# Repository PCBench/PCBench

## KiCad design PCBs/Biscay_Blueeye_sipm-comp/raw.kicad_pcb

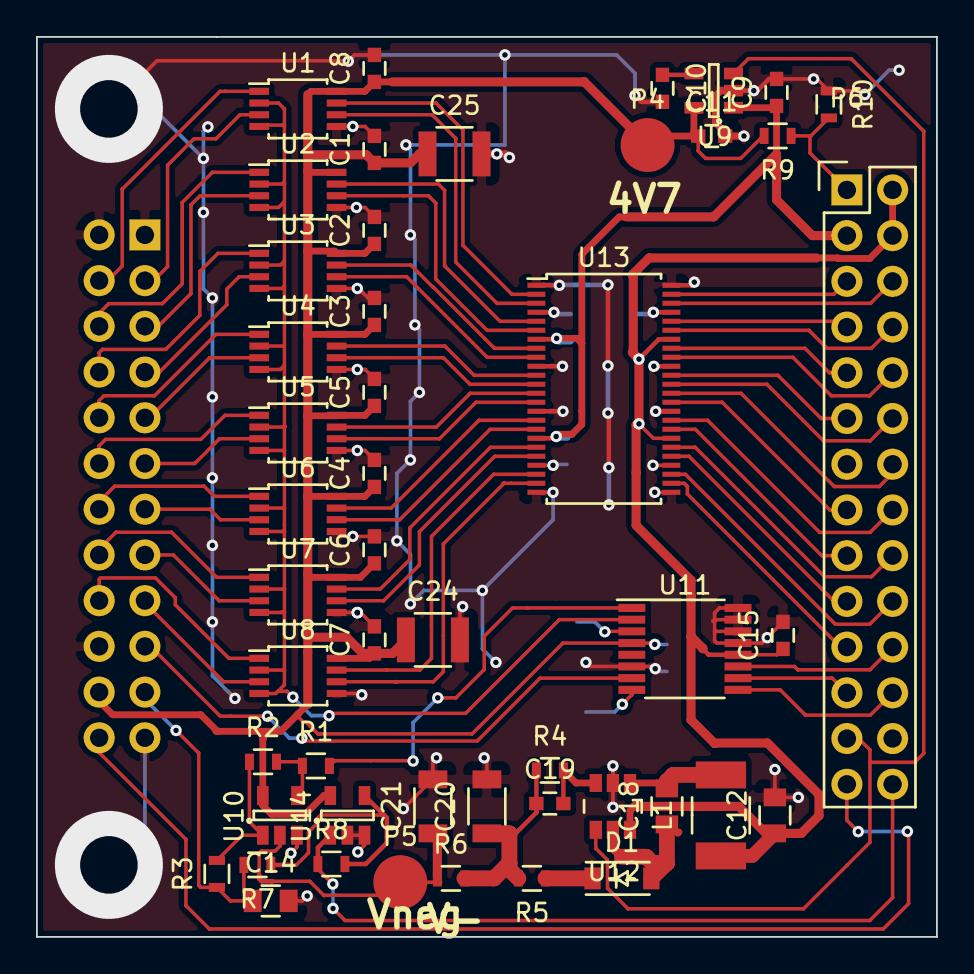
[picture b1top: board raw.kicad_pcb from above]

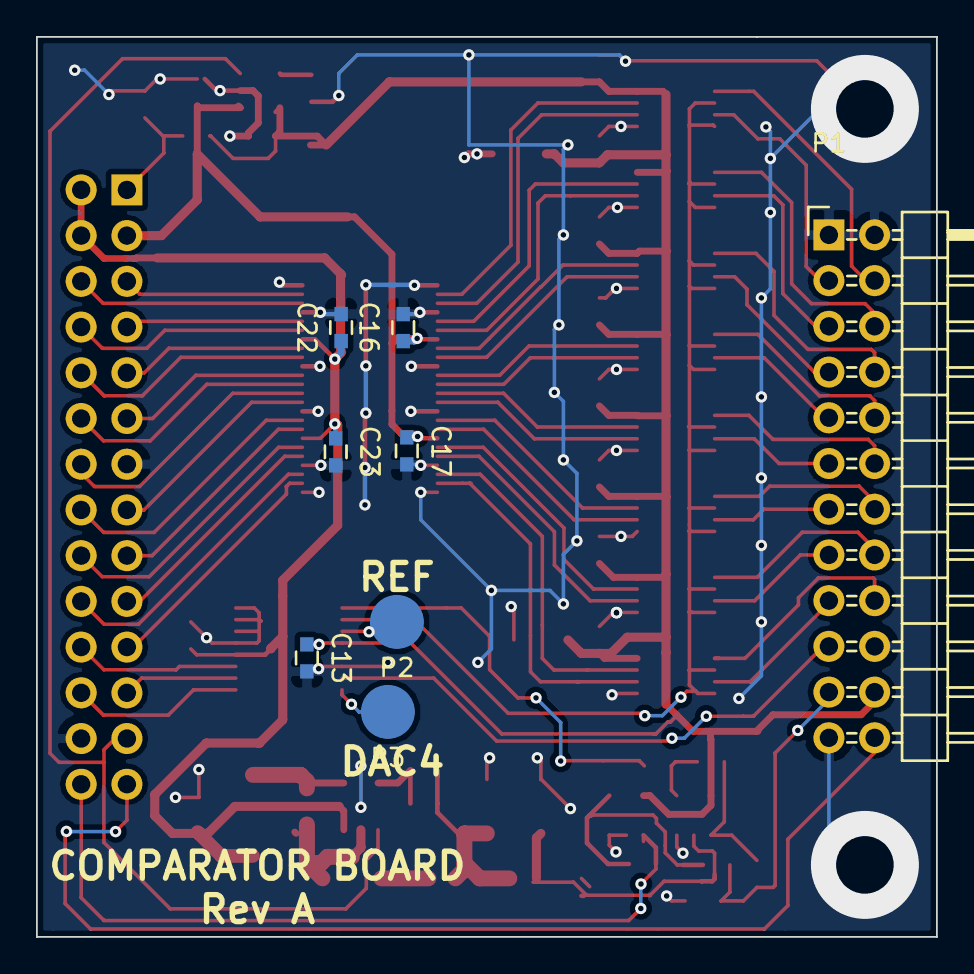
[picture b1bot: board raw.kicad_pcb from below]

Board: 2 copper layers, 50.0 x 50.0 mm, 57 parts (8 on the bottom side), 75 nets.

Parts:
C1, C2, C3, C4, C5, C6, C7, C8, C9, C11, C13, C15, C16, C17, C22, C23: 1u; C_0603
C10: 10n; C_0603
C12: 4.7u; C_0805
C14, C18: 0.1u; C_0805
C19: 5p; C_0603
C20, C21: 1u; C_1206
C24, C25: 22u; C_1210
D1: MBR0540; SOD-123
L1: 10u; Neosid_Inductor_SM-NE45_SMD1812
P1: CONN_02X12; Pin_Header_Angled_2x12
P2: REFO; Measurement_Point_Round-SMD-Pad_Big
P3: AUXDAC; Measurement_Point_Round-SMD-Pad_Big
P4: 5VA; Measurement_Point_Round-SMD-Pad_Big
P5: Vneg; Measurement_Point_Round-SMD-Pad_Big
P6: CONN_01X28; Pin_Header_Straight_2x14
R1, R3: 1k; R_0603
R2, R8: 15k; R_0603
R4: 3.4M; R_0603
R5: 39; R_0603
R6: 100; R_0603
R7: 100k; R_0603
R9, R10: 10k; R_0603
U1, U2, U3, U4, U5, U6, U7, U8: MAX9012; TSSOP-8_3x3mm_Pitch0.65mm
U9: LD3985M47R; SOT-23-5
U10: LT6015; SOT-23-5
U11: DAC7564; TSSOP-16_4.4x5mm_Pitch0.65mm
U12: LT3483; TSOT-6-MK06A
U13: SN74LVCH16T245; TSSOP-48_6.1x12.5mm_Pitch0.5mm
U14: LT6003; SOT-23-5

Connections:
+3V3: C12.1, C15.1, C22.1, C23.1, L1.1, P6.2, P6.4, U11.12, U12.6, U13.31, U13.42
+5V: C9.1, C16.1, C17.1, P6.3, U9.1, U13.7, U13.18
+5VA: C1.1, C2.1, C3.1, C4.1, C5.1, C6.1, C7.1, C8.1, C11.1, C13.1, C24.1, C25.1, P1.22, P4.1, R9.2, U1.8, U2.8, U3.8, U4.8, U5.8, U6.8, U7.8, U8.8, U9.5, U10.5, U11.4, U14.5
/AMP_1: P1.11, U5.3
/AMP_2: P1.15, U7.3
/AMP_3: P1.8, U3.1
/AMP_4: P1.9, U4.3
/AMP_5: P1.13, U6.3
/AMP_6: P1.16, U7.1
/AMP_7: P1.7, U3.3
/AMP_8: P1.10, U4.1
/AMP_9: P1.18, U8.1
/AMP_10: P1.17, U8.3
/AMP_11: P1.5, U2.3
/AMP_12: P1.6, U2.1
/AMP_13: P1.14, U6.1
/AMP_14: P1.12, U5.1
/AMP_15: P1.3, U1.3
/AMP_16: P1.4, U1.1
/COMP_1: U5.6, U13.14
/COMP_2: U7.6, U13.20
/COMP_3: U3.7, U13.8
/COMP_4: U4.6, U13.12
/COMP_5: U6.6, U13.17
/COMP_6: U7.7, U13.19
/COMP_7: U3.6, U13.9
/COMP_8: U4.7, U13.11
/COMP_9: U8.7, U13.22
/COMP_10: U8.6, U13.23
/COMP_11: U2.6, U13.6
/COMP_12: U2.7, U13.5
/COMP_13: U6.7, U13.16
/COMP_14: U5.7, U13.13
/COMP_15: U1.6, U13.3
/COMP_16: U1.7, U13.2
/DAC_Din: P6.22, U11.11
/DAC_SCLK: P6.23, U11.10
/DAC_~SYNC: P6.24, U11.9
/MON_5VA: P6.1, R9.1, R10.2
/OUT_1: P6.15, U13.35
/OUT_2: P6.19, U13.29
/OUT_3: P6.9, U13.41
/OUT_4: P6.12, U13.37
/OUT_5: P6.17, U13.32
/OUT_6: P6.18, U13.30
/OUT_7: P6.10, U13.40
/OUT_8: P6.11, U13.38
/OUT_9: P6.20, U13.27
/OUT_10: P6.21, U13.26
/OUT_11: P6.8, U13.43
/OUT_12: P6.7, U13.44
/OUT_13: P6.16, U13.33
/OUT_14: P6.14, U13.36
/OUT_15: P6.6, U13.46
/OUT_16: P6.5, U13.47
/TEMPS: P1.24, P6.27
/Vb_MON: P6.28, R8.1, U14.1
GND: C1.2, C2.2, C3.2, C4.2, C5.2, C6.2, C7.2, C8.2, C9.2, C10.2, C11.2, C12.2, C13.2, C14.2, C15.2, C16.2, C17.2, C20.2, C21.2, C22.2, C23.2, C24.2, C25.2, P1.1, P1.2, P1.20, P1.23, P6.13, P6.26, R10.1, U1.5, U2.5, U3.5, U4.5, U5.5, U6.5, U7.5, U8.5, U9.2, U10.3, U11.6, U11.13, U11.14, U11.15, U11.16, U12.2, U13.1, U13.4, U13.10, U13.15, U13.21, U13.24, U13.25, U13.28, U13.34, U13.39, U13.45, U13.48, U14.2, U14.3
unnamed: C10.1, U9.4
unnamed: C18.1, D1.2, U12.5
unnamed: C18.2, L1.2, U12.1
unnamed: C19.1, C20.1, R4.1, R5.2, R6.2
unnamed: C19.2, R4.2, U12.3
unnamed: D1.1, R5.1
unnamed: P2.1, U11.3
unnamed: P3.1, U11.8
unnamed: R1.1, R2.2, U10.4
unnamed: R2.1, R3.2, U10.1
unnamed: R7.1, R8.2, U14.4
REG_EN: P6.25, U9.3, U12.4
Vbias: C14.1, P1.21, R3.1, R7.2
Vbias_SET: R1.2, U11.1
Vmid: P1.19, U11.7
Vneg: C21.1, P5.1, R6.1, U10.2
Vset: U1.2, U1.4, U2.2, U2.4, U3.2, U3.4, U4.2, U4.4, U5.2, U5.4, U6.2, U6.4, U7.2, U7.4, U8.2, U8.4, U11.2

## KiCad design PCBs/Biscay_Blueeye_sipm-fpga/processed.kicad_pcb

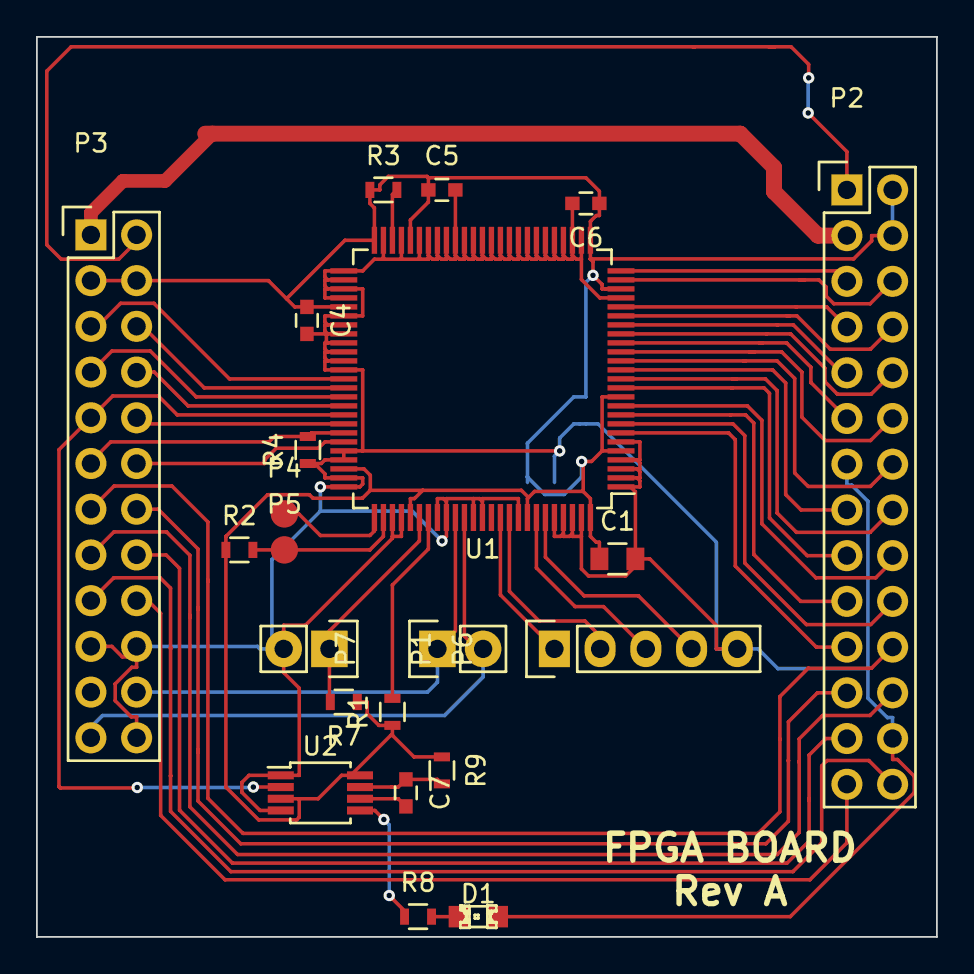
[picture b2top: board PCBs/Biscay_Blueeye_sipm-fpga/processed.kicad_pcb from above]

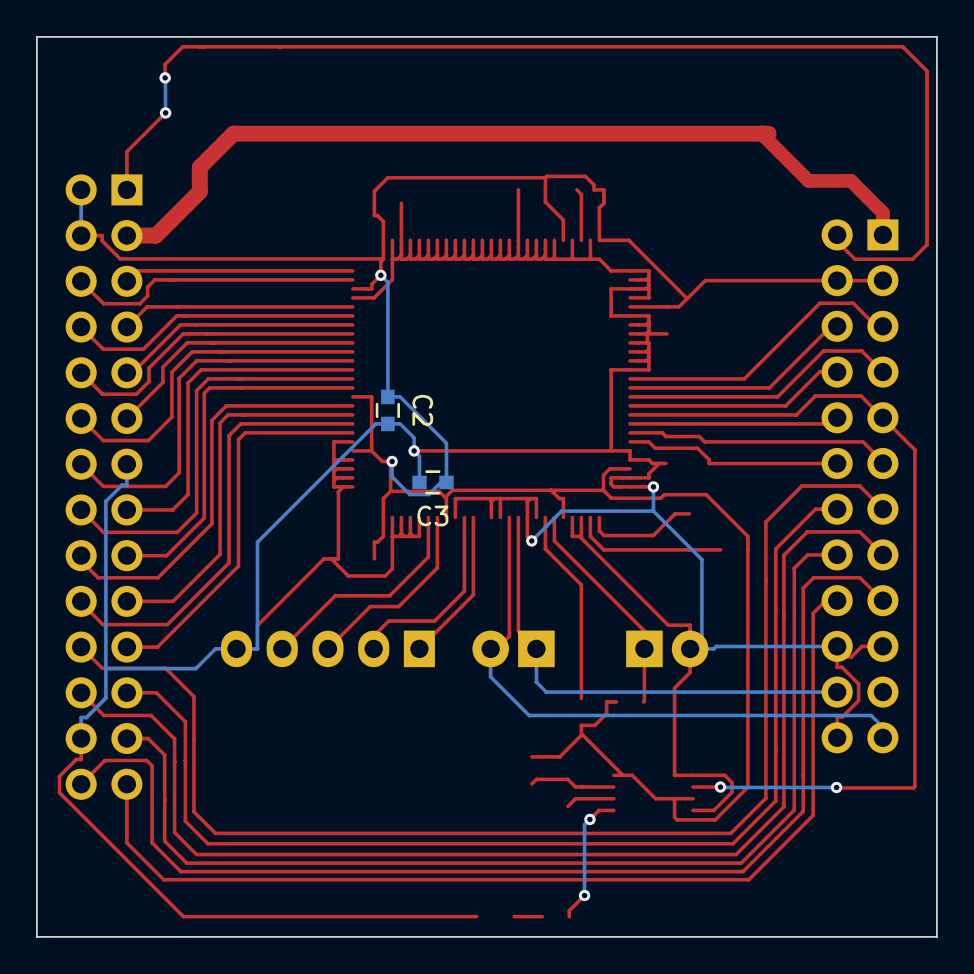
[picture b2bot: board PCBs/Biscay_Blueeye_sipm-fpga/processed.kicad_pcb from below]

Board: 2 copper layers, 50.0 x 50.0 mm, 24 parts (2 on the bottom side), 49 nets.

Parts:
C1: 10u; C_0805
C2, C3, C4, C5, C6, C7: 1u; C_0603
D1: LED; LED-0805
P1: PROG; Pin_Header_Straight_1x02
P2: CONN_02X14; Pin_Header_Straight_2x14
P3: CONN_02X12; Pin_Header_Straight_2x12
P4: DONE; Measurement_Point_Round-SMD-Pad_Small
P5: INITN; Measurement_Point_Round-SMD-Pad_Small
P6: JTAG; Pin_Header_Straight_1x05
P7: I2C; Pin_Header_Straight_1x02
R1, R2, R3, R4, R7: 10k; R_0603
R8: 330; R_0603
R9: 220k; R_0603
U1: LCMXO2-2000-TQFP100; TQFP-100_14x14mm_Pitch0.5mm
U2: SN74LVC1G123; MSOP-8_3x3mm_Pitch0.65mm

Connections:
+3V3: C1.1, C2.1, C3.1, C4.1, C5.1, C6.1, P2.2, P2.4, P3.3, P3.4, R1.1, R2.1, R3.1, R7.1, R9.1, U1.5, U1.11, U1.23, U1.26, U1.46, U1.50, U1.55, U1.73, U1.80, U1.93, U1.100, U2.3, U2.8
+5V: P2.3, P3.1
/CAPTD: P3.10, U1.68
/CLR: P3.11, R4.2, U1.69
/DAC_MOSI: P2.22, P3.13
/DAC_SCLK: P2.23, P3.14
/DAC_~SYNC: P2.24, P3.15
/DONE: P4.1, U1.76
/INITN: P5.1, R2.2, U1.77
/JTAGENB: R1.2, U1.82
/JTAG_TCK: P6.2, U1.91
/JTAG_TDI: P6.3, U1.94
/JTAG_TDO: P6.4, U1.95
/JTAG_TMS: P6.1, U1.90
/MON_5VA: P2.1, P3.2
/OUT_1: P2.15, U1.14
/OUT_2: P2.19, U1.9
/OUT_3: P2.9, U1.19
/OUT_4: P2.12, U1.16
/OUT_5: P2.17, U1.12
/OUT_6: P2.18, U1.10
/OUT_7: P2.10, U1.18
/OUT_8: P2.11, U1.17
/OUT_9: P2.20, U1.8
/OUT_10: P2.21, U1.7
/OUT_11: P2.8, U1.20
/OUT_12: P2.7, U1.21
/OUT_13: P2.16, U1.13
/OUT_14: P2.14, U1.15
/OUT_15: P2.6, U1.24
/OUT_16: P2.5, U1.25
/PROGRAMN: P1.1, R7.2, U1.81
/REG_EN: P2.25, P3.16
/SCL: P3.23, P7.2, U1.86
/SDA: P3.22, P7.1, U1.85
/SN: R3.2, U1.48
/SPI_MISO: P3.8, U1.66
/SPI_MOSI: P3.7, U1.65
/SPI_SCK: P3.5, U1.63
/SPI_~CS0: P3.6, U1.64
/SPI_~CS1: P3.12, U1.70
/TEMPS: P2.27, P3.18
/TRIGD: P3.9, U1.67, U2.2
/Vb_MON: P2.28, P3.17
GND: C1.2, C2.2, C3.2, C4.2, C5.2, C6.2, D1.2, P1.2, P2.13, P2.26, P3.19, P3.20, P3.24, P6.5, R4.1, U1.1, U1.2, U1.3, U1.4, U1.6, U1.22, U1.27, U1.28, U1.29, U1.30, U1.31, U1.32, U1.33, U1.34, U1.35, U1.36, U1.37, U1.38, U1.39, U1.40, U1.41, U1.42, U1.43, U1.44, U1.45, U1.47, U1.49, U1.51, U1.52, U1.53, U1.54, U1.56, U1.57, U1.58, U1.59, U1.60, U1.61, U1.62, U1.71, U1.72, U1.74, U1.75, U1.78, U1.79, U1.83, U1.84, U1.87, U1.88, U1.92, U1.96, U1.97, U1.98, U1.99, U2.1, U2.4
unnamed: C7.1, R9.2, U2.7
unnamed: C7.2, U2.6
unnamed: D1.1, R8.2
unnamed: R8.1, U2.5

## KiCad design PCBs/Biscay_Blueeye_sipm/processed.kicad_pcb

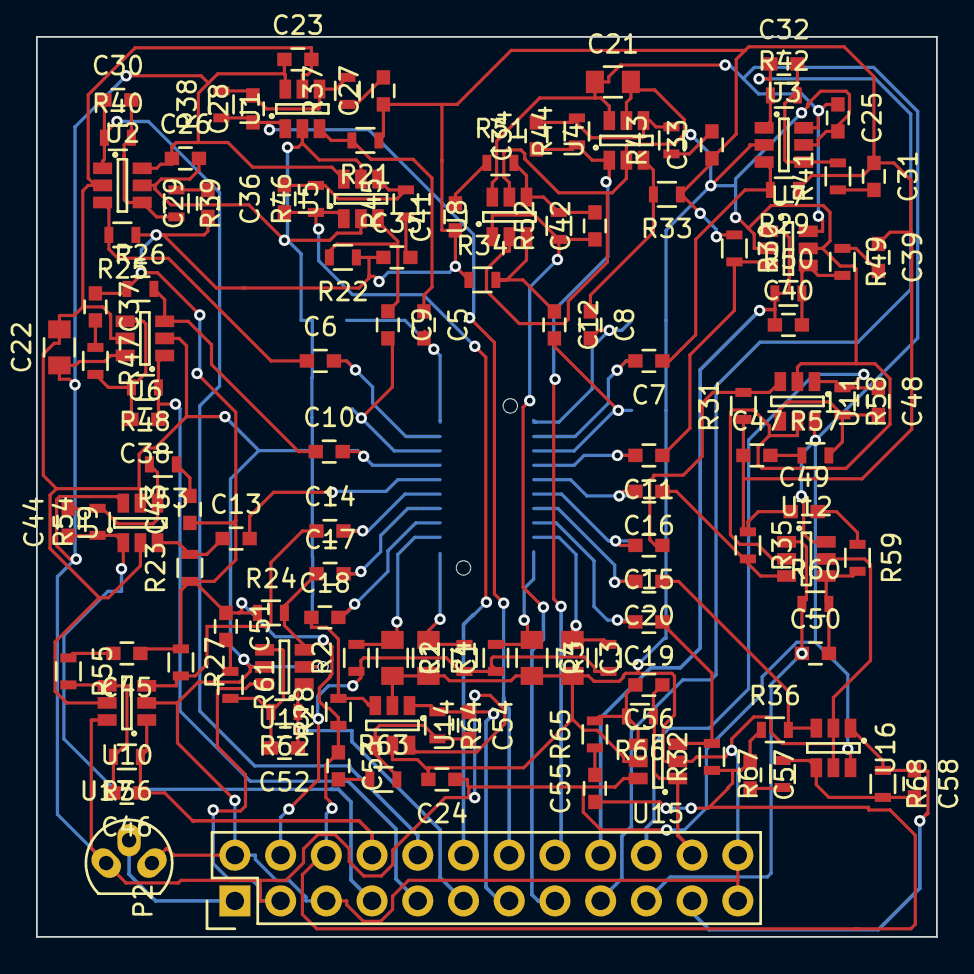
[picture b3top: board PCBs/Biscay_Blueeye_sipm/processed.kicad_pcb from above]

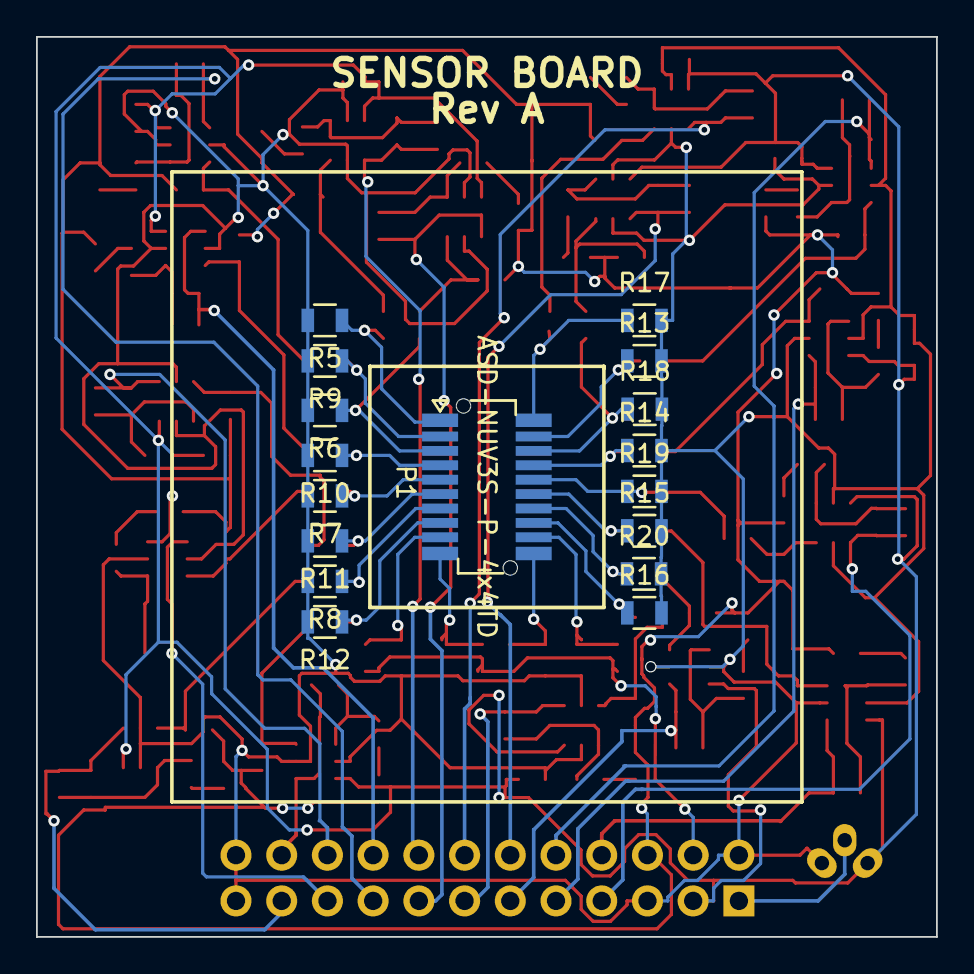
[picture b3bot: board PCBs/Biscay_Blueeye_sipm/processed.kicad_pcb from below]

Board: 4 copper layers, 50.0 x 50.0 mm, 145 parts (17 on the bottom side), 89 nets.

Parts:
C1, C2, C3, C4: 100n; C_0805
C5, C6, C7, C8, C9, C10, C11, C12, C13, C14, C15, C16, C17, C18, C19, C20: 100n; C_0603
C21, C22: 10u; C_0805
C23, C24, C25, C26: 1u; C_0603
C27, C29, C31, C33, C35, C37, C39, C41, C43, C45, C47, C49, C51, C53, C55, C57: 10n; C_0603
C28, C30, C32, C34, C36, C38, C40, C42, C44, C46, C48, C50, C52, C54, C56, C58: DNP; C_0603
P1: ASD-NUV3S-P-4x4TD; JAE-IL-WX-20S-VF-BE
P2: CONN_02X12; Pin_Header_Straight_2x12
R1, R2, R3, R4, R21, R22, R23, R24, R25, R26, R27, R28, R29, R30, R31, R32, R33, R34, R35, R36: 10k; R_0603
R5, R6, R7, R8, R9, R10, R11, R12, R13, R14, R15, R16, R17, R18, R19, R20: 200?; R_0805
R37, R39, R41, R43, R45, R47, R49, R51, R53, R55, R57, R59, R61, R63, R65, R67: 220; R_0603
R38, R40, R42, R44, R46, R48, R50, R52, R54, R56, R58, R60, R62, R64, R66, R68: 6.8k; R_0603
U1, U2, U3, U4, U5, U6, U7, U8, U9, U10, U11, U12, U13, U14, U15, U16: LT6230-10; SOT-23-6
U17: LMT84; TO-92_Molded_Narrow_Oval

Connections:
+5V: C21.1, C22.1, C23.1, C24.1, C25.1, C26.1, P2.3, U1.6, U2.6, U3.6, U4.6, U5.6, U6.6, U7.6, U8.6, U9.6, U10.6, U11.6, U12.6, U13.6, U14.6, U15.6, U16.6, U17.1
/Amplifier 1/IN: C5.1, R21.2, U1.3
/Amplifier 1/OUT: C28.1, P2.14, R38.1, U1.1
/Amplifier 2/IN: C6.1, R25.2, U2.3
/Amplifier 2/OUT: C30.1, P2.10, R40.1, U2.1
/Amplifier 3/IN: C7.1, R29.2, U3.3
/Amplifier 3/OUT: C32.1, P2.17, R42.1, U3.1
/Amplifier 4/IN: C8.1, R33.2, U4.3
/Amplifier 4/OUT: C34.1, P2.16, R44.1, U4.1
/Amplifier 5/IN: C9.1, R22.2, U5.3
/Amplifier 5/OUT: C36.1, P2.12, R46.1, U5.1
/Amplifier 6/IN: C10.1, R26.2, U6.3
/Amplifier 6/OUT: C38.1, P2.9, R48.1, U6.1
/Amplifier 7/IN: C11.1, R30.2, U7.3
/Amplifier 7/OUT: C40.1, P2.18, R50.1, U7.1
/Amplifier 8/IN: C12.1, R34.2, U8.3
/Amplifier 8/OUT: C42.1, P2.15, R52.1, U8.1
/Amplifier 9/IN: C13.1, R23.2, U9.3
/Amplifier 9/OUT: C44.1, P2.7, R54.1, U9.1
/Amplifier 10/IN: C14.1, R27.2, U10.3
/Amplifier 10/OUT: C46.1, P2.8, R56.1, U10.1
/Amplifier 11/IN: C15.1, R31.2, U11.3
/Amplifier 11/OUT: C48.1, P2.20, R58.1, U11.1
/Amplifier 12/IN: C16.1, R35.2, U12.3
/Amplifier 12/OUT: C50.1, P2.19, R60.1, U12.1
/Amplifier 13/IN: C17.1, R24.2, U13.3
/Amplifier 13/OUT: C52.1, P2.11, R62.1, U13.1
/Amplifier 14/IN: C18.1, R28.2, U14.3
/Amplifier 14/OUT: C54.1, P2.13, R64.1, U14.1
/Amplifier 15/IN: C19.1, R32.2, U15.3
/Amplifier 15/OUT: C56.1, P2.22, R66.1, U15.1
/Amplifier 16/IN: C20.1, R36.2, U16.3
/Amplifier 16/OUT: C58.1, P2.21, R68.1, U16.1
/TEMPS: P2.1, U17.2
GND: C1.2, C2.2, C3.2, C4.2, C21.2, C22.2, C23.2, C24.2, C25.2, C26.2, P2.2, P2.5, P2.23, P2.24, R5.2, R6.2, R7.2, R8.2, R9.2, R10.2, R11.2, R12.2, R13.2, R14.2, R15.2, R16.2, R17.2, R18.2, R19.2, R20.2, U1.2, U1.5, U2.2, U2.5, U3.2, U3.5, U4.2, U4.5, U5.2, U5.5, U6.2, U6.5, U7.2, U7.5, U8.2, U8.5, U9.2, U9.5, U10.2, U10.5, U11.2, U11.5, U12.2, U12.5, U13.2, U13.5, U14.2, U14.5, U15.2, U15.5, U16.2, U16.5, U17.3
unnamed: C1.1, P1.11, R1.2
unnamed: C2.1, P1.12, R2.2
unnamed: C3.1, P1.9, R3.2
unnamed: C4.1, P1.10, R4.2
unnamed: C5.2, P1.20, R17.1
unnamed: C6.2, P1.19, R13.1
unnamed: C7.2, P1.2, R9.1
unnamed: C8.2, P1.1, R5.1
unnamed: C9.2, P1.18, R18.1
unnamed: C10.2, P1.17, R14.1
unnamed: C11.2, P1.4, R10.1
unnamed: C12.2, P1.3, R6.1
unnamed: C13.2, P1.16, R19.1
unnamed: C14.2, P1.15, R15.1
unnamed: C15.2, P1.6, R11.1
unnamed: C16.2, P1.5, R7.1
unnamed: C17.2, P1.14, R20.1
unnamed: C18.2, P1.13, R16.1
unnamed: C19.2, P1.8, R12.1
unnamed: C20.2, P1.7, R8.1
unnamed: C27.2, R37.1
unnamed: C28.2, R37.2, R38.2, U1.4
unnamed: C29.2, R39.1
unnamed: C30.2, R39.2, R40.2, U2.4
unnamed: C31.2, R41.1
unnamed: C32.2, R41.2, R42.2, U3.4
unnamed: C33.2, R43.1
unnamed: C34.2, R43.2, R44.2, U4.4
unnamed: C35.2, R45.1
unnamed: C36.2, R45.2, R46.2, U5.4
unnamed: C37.2, R47.1
unnamed: C38.2, R47.2, R48.2, U6.4
unnamed: C39.2, R49.1
unnamed: C40.2, R49.2, R50.2, U7.4
unnamed: C41.2, R51.1
unnamed: C42.2, R51.2, R52.2, U8.4
unnamed: C43.2, R53.1
unnamed: C44.2, R53.2, R54.2, U9.4
unnamed: C45.2, R55.1
unnamed: C46.2, R55.2, R56.2, U10.4
unnamed: C47.2, R57.1
unnamed: C48.2, R57.2, R58.2, U11.4
unnamed: C49.2, R59.1
unnamed: C50.2, R59.2, R60.2, U12.4
unnamed: C51.2, R61.1
unnamed: C52.2, R61.2, R62.2, U13.4
unnamed: C53.2, R63.1
unnamed: C54.2, R63.2, R64.2, U14.4
unnamed: C55.2, R65.1
unnamed: C56.2, R65.2, R66.2, U15.4
unnamed: C57.2, R67.1
unnamed: C58.2, R67.2, R68.2, U16.4
Vbias: P2.4, R1.1, R2.1, R3.1, R4.1
Vmid: C27.1, C29.1, C31.1, C33.1, C35.1, C37.1, C39.1, C41.1, C43.1, C45.1, C47.1, C49.1, C51.1, C53.1, C55.1, C57.1, P2.6, R21.1, R22.1, R23.1, R24.1, R25.1, R26.1, R27.1, R28.1, R29.1, R30.1, R31.1, R32.1, R33.1, R34.1, R35.1, R36.1

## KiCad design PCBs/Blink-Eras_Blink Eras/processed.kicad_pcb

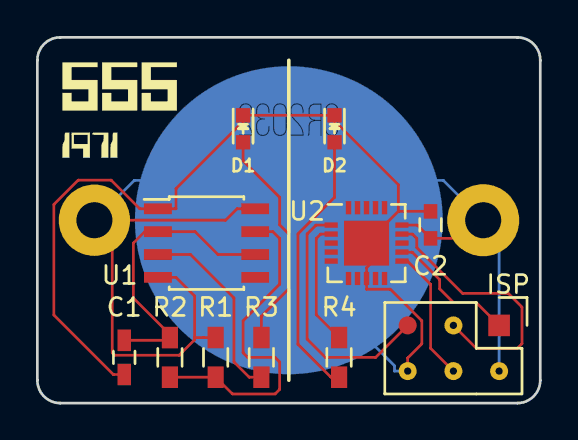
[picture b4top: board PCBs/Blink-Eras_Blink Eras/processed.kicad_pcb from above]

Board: 2 copper layers, 27.9 x 20.3 mm, 12 parts (1 on the bottom side), 12 nets.

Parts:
BT1: CR2032; Big_Pad_Battery
C1: 1µ; C_0603_HandSoldering
C2: 1µ; C_0603
D1: Red; LED_0603
D2: Green; LED_0603
P1: ISP; ISP_Pogo_5-thru
R1: 1K; R_0603_HandSoldering
R2: 470K; R_0603_HandSoldering
R3: 68; R_0603_HandSoldering
R4: 56; R_0603_HandSoldering
U1: ICM7555; SOIC-8_3.9x4.9mm_Pitch1.27mm
U2: ATTINY85-M; QFN-20-1EP_4x4mm_Pitch0.5mm

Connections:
/MISO: P1.1, U2.12
/MOSI: P1.4, U2.11
/SCK: P1.3, U2.14
/~RESET~: P1.5, U2.1
GND: BT1.2, C1.2, C2.2, D1.1, D2.1, P1.6, U1.1, U2.8
unnamed: C1.1, R2.2, U1.2, U1.6
unnamed: D1.2, R3.2
unnamed: D2.2, R4.2
unnamed: R1.2, R2.1, U1.7
unnamed: R3.1, U1.3
unnamed: R4.1, U2.2
VCC: BT1.1, C2.1, P1.2, R1.1, U1.4, U1.8, U2.15

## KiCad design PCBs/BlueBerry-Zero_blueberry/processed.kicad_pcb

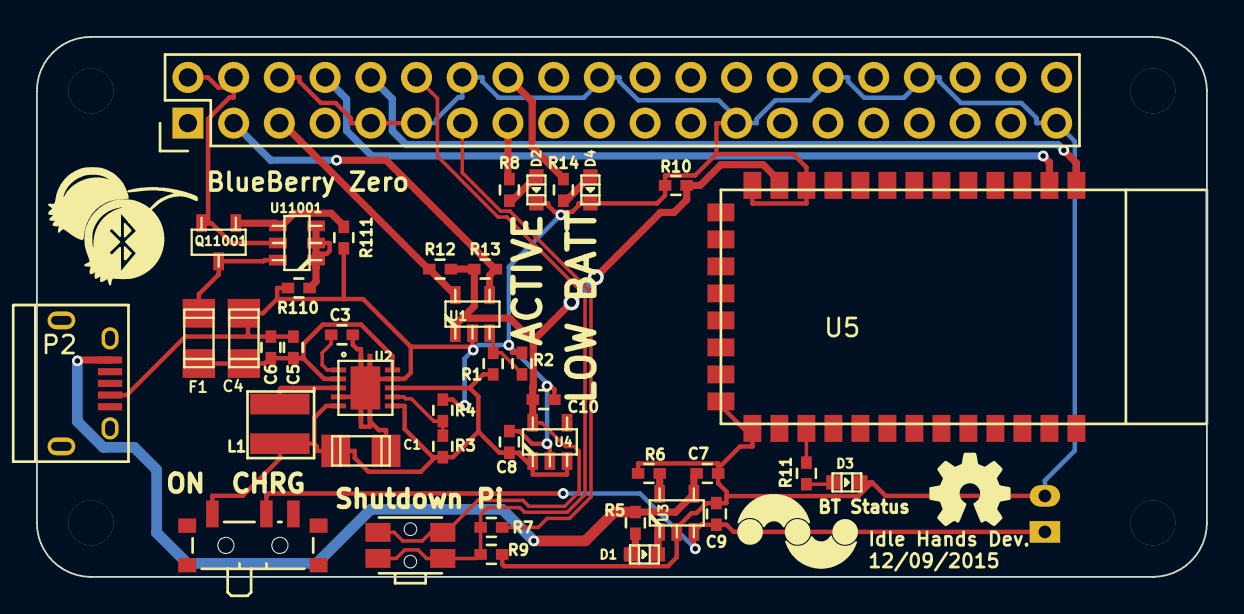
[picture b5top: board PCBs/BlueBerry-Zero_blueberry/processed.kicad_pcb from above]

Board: 2 copper layers, 65.0 x 30.0 mm, 43 parts (1 on the bottom side), 29 nets.

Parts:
C1, C4: 10uF; c_1206
C3, C6: 0.1uF; C_0402_Hand
C5: 1uF; C_0402_Hand
C7, C9: 4.7uF; C_0402_Hand
C8, C10: 1.0uf; C_0402_Hand
D1, D2, D3, D4: Led_Small; Led_0603
F1: FUSE; c_1206
L1: 2.2uH; I_1212
P1: Raspberry_Pi_+_Conn; Pin_Header_Straight_2x20
P2: USB_B; USB_Micro-B
P3: CONN_01X02; Connectors_JST_S2B-PH-K
Q11001: BSS138; SOT23
R1: 470K; R_0402_Hand
R2: 1.7M; R_0402_Hand
R3: 3.4M; R_0402_Hand
R4: 250k; R_0402_Hand
R5, R7, R8, R11, R14: 1K; R_0402_Hand
R6: 2K; R_0402_Hand
R9, R10: 10K; R_0402_Hand
R12, R13: 22K; R_0402_Hand
R110: 10k; R_0402_Hand
R111: 47k; R_0402_Hand
SW1: Switch_SPDT_x2; SW_SPDT_PCM12
SW2: SW_PUSH; SW_SPST_EVQP7C
U1: MCP3021; sot23-5
U2: TPS61202; PVSON-10
U3: MCP73831; sot23-5
U4: TLV71333DBV; sot23-5
U5: HC-06
U11001: DMMT5401; sot23-6

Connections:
+3V3: C10.1, R10.2, R12.1, R13.1, SW2.1, U1.1, U4.5, U5.12
+5V: F1.2, Q11001.3, U11001.6
/BATT: C9.1, P3.1, SW1.2, U3.3
/BATT5V: C4.1, C5.1, C6.1, F1.1, U2.2, U2.10
/LOW_BATT_LED: P1.16, R14.2
/PI_I2C_SCL: P1.5, R12.2, U1.5
/PI_I2C_SDA: P1.3, R13.2, U1.4
/PI_UART_RXD: P1.10, U5.1
/PI_UART_TXD: P1.8, U5.2
/SAFESHUT_LED: P1.15, R8.2
/SHUTDOWN: P1.13, R7.1
/USB5V: C7.1, P2.1, R5.2, U3.4
/UVLO: R3.2, R4.1, U2.7
/UVSHUTDOWN: P1.12, R7.2, R9.1, SW2.2
/VBATT: C1.1, C8.1, L1.1, R1.1, R3.1, SW1.1, U2.5, U2.6, U2.8, U4.1, U4.3
/sheet56654A17/5V_MCU: P1.2, P1.4, Q11001.2, U11001.5
GND: C1.2, C3.2, C4.2, C5.2, C6.2, C7.2, C8.2, C9.2, C10.2, D2.1, D3.1, D4.1, P1.6, P1.9, P1.11, P1.14, P1.20, P1.25, P1.30, P1.34, P1.39, P2.4, P3.2, R2.2, R4.2, R6.2, R9.2, R10.1, R110.2, R111.2, U1.2, U2.4, U2.9, U3.2, U4.2, U5.11, U5.13, U5.21, U5.22
unnamed: C3.1, U2.1
unnamed: D1.1, U3.1
unnamed: D1.2, R5.1
unnamed: D2.2, R8.1
unnamed: D3.2, R11.1
unnamed: D4.2, R14.1
unnamed: L1.2, U2.3
unnamed: Q11001.1, R111.1, U11001.4
unnamed: R1.2, R2.1, U1.3
unnamed: R6.1, U3.5
unnamed: R11.2, U5.24
unnamed: R110.1, U11001.1, U11001.2, U11001.3

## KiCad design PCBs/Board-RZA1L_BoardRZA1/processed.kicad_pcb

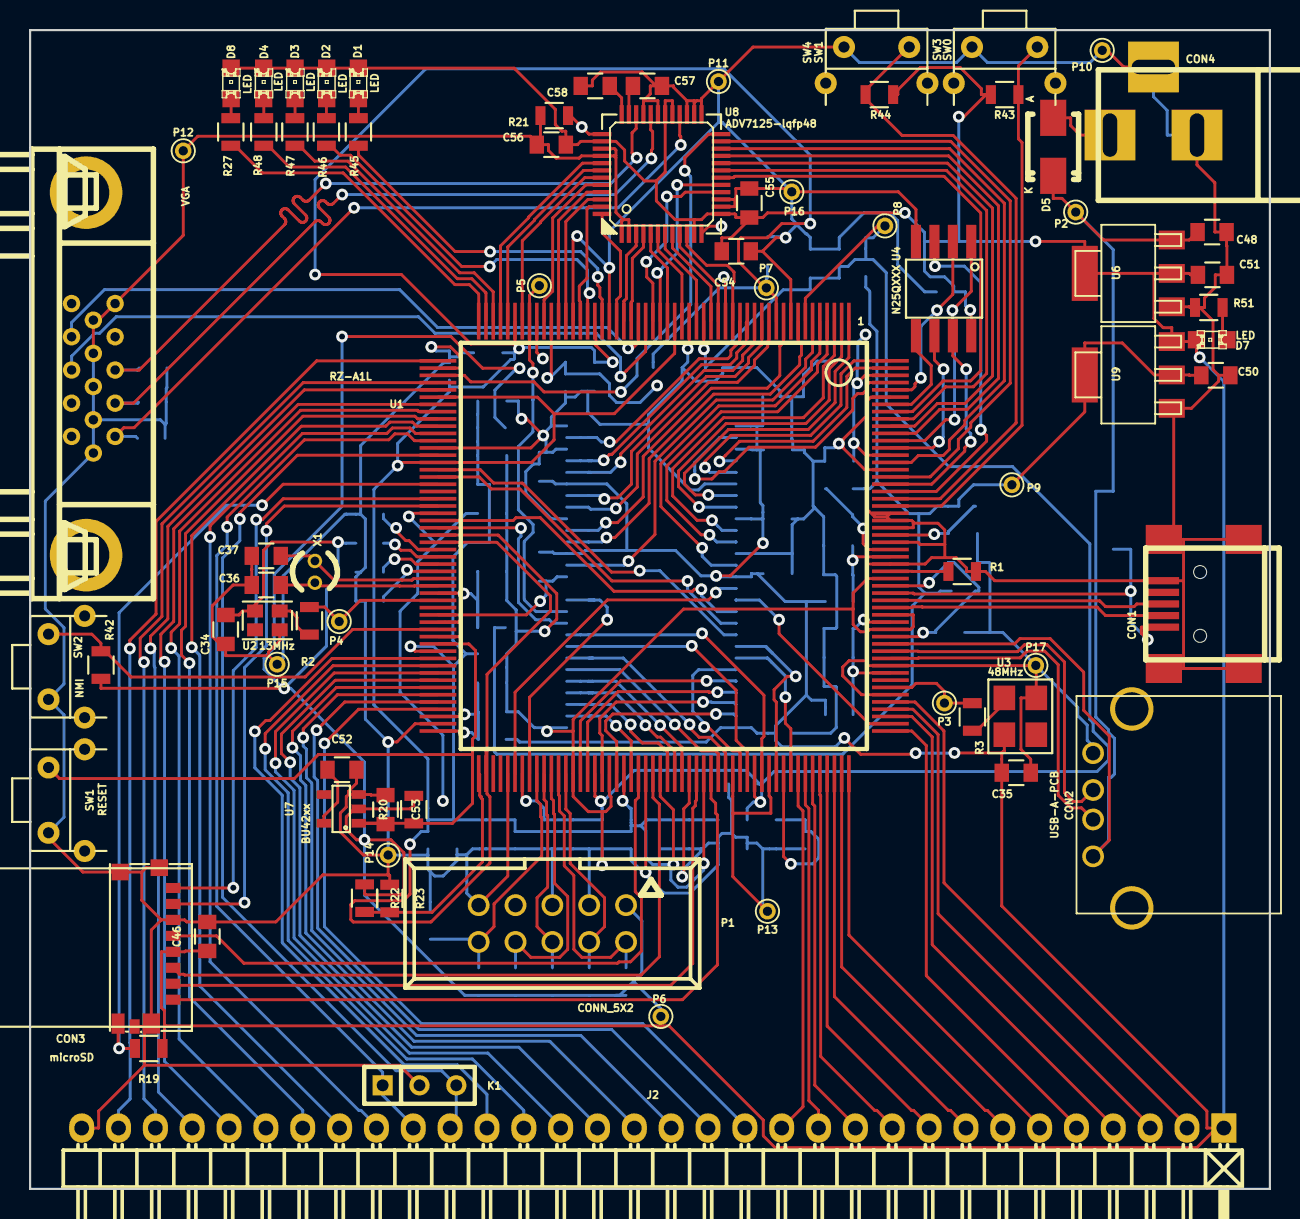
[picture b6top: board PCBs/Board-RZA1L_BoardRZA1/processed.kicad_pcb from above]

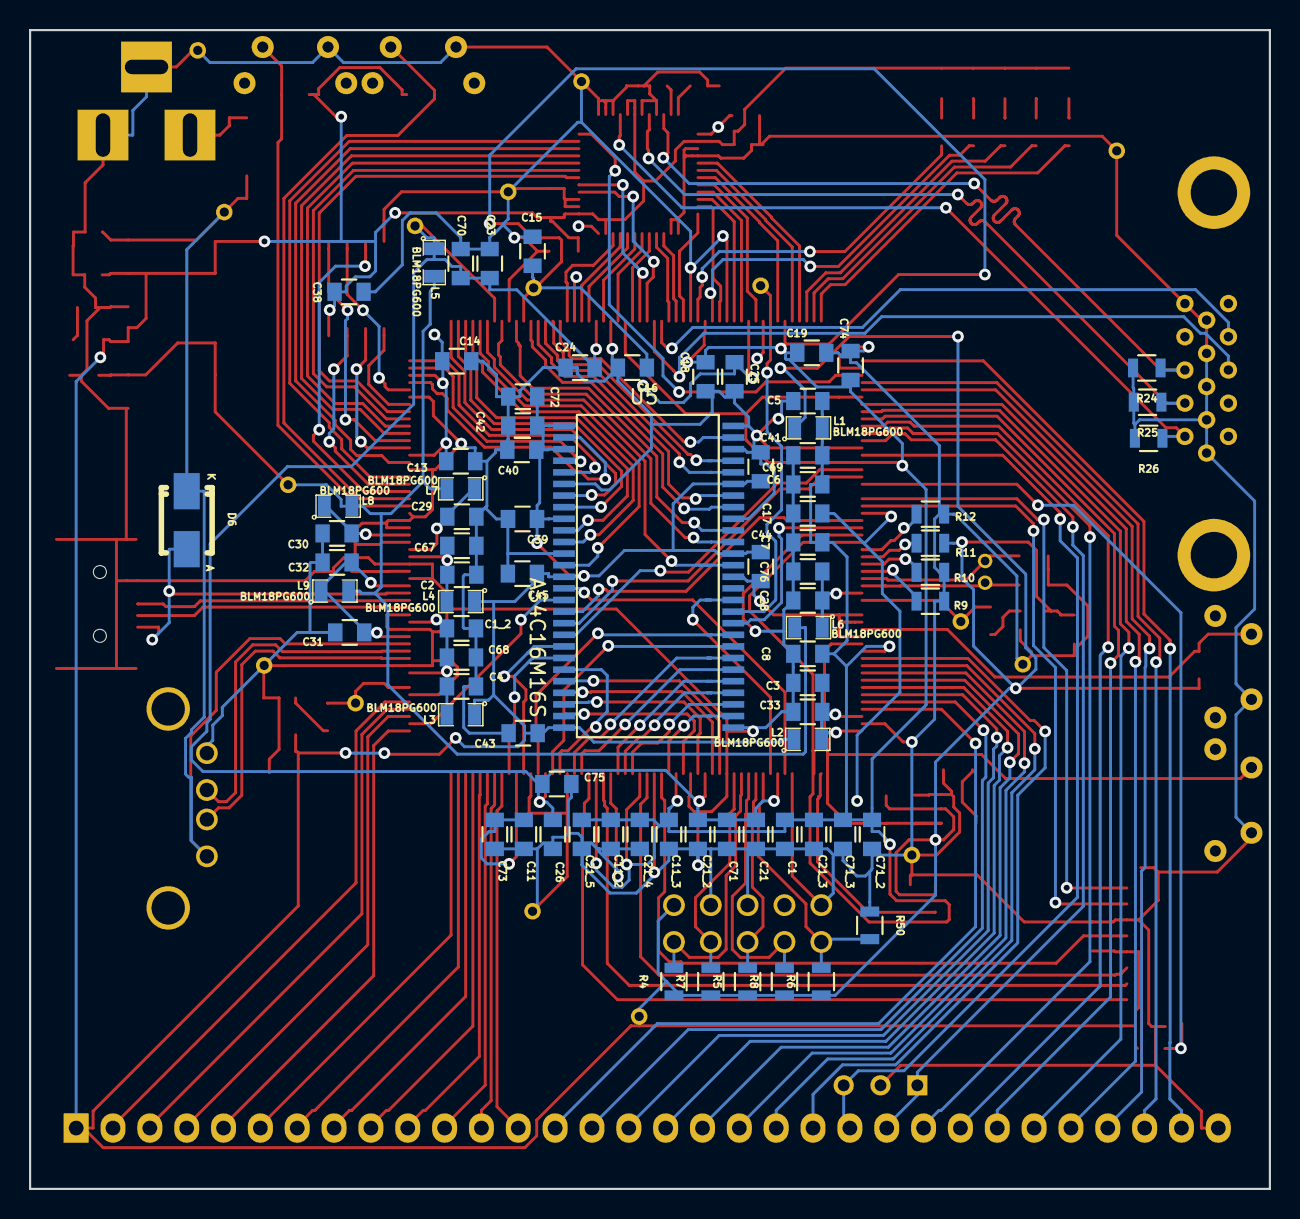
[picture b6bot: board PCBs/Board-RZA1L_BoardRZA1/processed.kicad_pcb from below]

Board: 4 copper layers, 85.5 x 79.9 mm, 154 parts (78 on the bottom side), 167 nets.

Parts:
C1, C1_2, C2, C3, C4, C5, C6, C7, C8, C11, C11_2, C11_3, C13, C14, C15, C16, C17, C18, C19, C21, C21_2, C21_3, C21_4, C21_5, C23, C24, C25, C26, C28, C29, C30, C31, C32, C33, C34, C35, C38, C39, C40, C41, C42, C43, C44, C45, C51, C52, C54, C55, C56, C57, C58: 100n; C_0805
C36, C37: 10p; C_0805
C46, C50, C53: 1u; C_0805
C48, C67, C68, C69, C70, C71_3: 10u; C_0805
C71, C71_2, C72, C73, C74, C75, C76: 100p; C_0805
CON1: USB-MINI-B; USB_MINI_B
CON2: USB-A-PCB; USB_A
CON3: microSD
CON4: BARREL_JACK
D1, D2, D3, D4, D7, D8: LED; LED-0805
D5, D6: MBRA210; Diode-SMA_Standard
J1: VGA; DB_15F-VGA
J2: SUPP32; Pin_Header_Angled_1x32
K1: CONN_3; SIL-3
L1, L2, L3, L4, L5, L6, L7, L8, L9: BLM18PG600; SM0805
P1: CONN_5X2; VASCH5x2
P2, P3, P4, P5, P6, P7, P8, P9, P10, P11, P12, P13, P14, P15, P16, P17: CONN_1; PINTST
R1: 5K6; R_0805
R2, R3, R51: 220R; R_0805
R4, R5, R6, R7, R8, R9, R10, R11, R12, R19, R20, R22, R23, R42, R43, R44, R50: 10k; R_0805
R21: 560R; R_0805
R24, R25, R26: 75R; R_0805
R27, R45, R46, R47, R48: 1k; R_0805
SW1: RESET; RigthAnglePush
SW2: NMI; RigthAnglePush
SW3: SW0; RigthAnglePush
SW4: SW1; RigthAnglePush
U1: RZ-A1L; PQFP208
U2: 13MHz; OSC_2x2p5
U3: 48MHz; OSC_4PIN
U4: N25QXXX; SOP2-8
U5: AS4C16M16S; TSOP_II_54
U6: NCP1117ST33T3G; sot223
U7: BU42xx; SSOP-5
U8: ADV7125-lqfp48; lqfp48
U9: NCP1117ST12T3G; sot223
X1: 32.768k; Crystal_Round_Vertical_3mm

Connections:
+1.2V: C50.1, L5.2, L6.2, L7.2, L8.2, L9.2, P9.1, U9.2
+3.3V: C34.1, C35.1, C38.1, C39.1, C40.1, C41.1, C42.1, C43.1, C44.1, C45.1, C46.1, C51.1, C54.2, C55.2, C56.2, C72.1, CON3.4, D1.2, D2.2, D3.2, D4.2, D7.2, D8.2, J2.1, L1.1, L2.1, L3.1, L4.1, P1.1, P6.1, R4.1, R5.1, R6.1, R7.1, R8.1, R11.1, R19.1, R20.2, R22.1, R42.2, R43.2, R44.2, U2.4, U3.4, U4.8, U5.1, U5.3, U5.9, U5.14, U5.27, U5.43, U5.49, U6.2, U7.2, U8.11, U8.13, U8.29, U8.30, U8.38, U9.3
/+5v: C48.1, CON2.1, D5.2, D6.2, P2.1, U1.169, U6.3
/AVcc: C3.1, C33.2, L2.2, U1.102, U1.104
/DCIN: CON4.1, D5.1
/DM_CLK: R10.2, U1.81
/D_D+: CON1.3, U1.175
/D_D-: CON1.2, U1.174
/H_D+: CON2.3, U1.168
/H_D-: CON2.2, U1.167
/JTAG_TCK: P1.4, R7.2, U1.117
/JTAG_TDI: P1.8, R8.2, U1.115
/JTAG_TDO: P1.6, R5.2, U1.114
/JTAG_TMS: P1.2, R4.2, U1.116
/JTAG_TRST: P1.10, R6.2, R50.2, U1.113
/LCD_DATA0: U1.192, U8.23
/LCD_DATA1: U1.194, U8.22
/LCD_DATA2: U1.198, U8.21
/LCD_DATA3: U1.199, U8.20
/LCD_DATA4: U1.200, U8.19
/LCD_DATA5: U1.201, U8.18
/LCD_DATA6: U1.27, U8.17
/LCD_DATA7: U1.28, U8.16
/LCD_DATA8: U1.17, U8.10
/LCD_DATA9: U1.19, U8.9
/LCD_DATA10: U1.20, U8.8
/LCD_DATA11: U1.22, U8.7
/LCD_DATA12: U1.24, U8.6
/LCD_DATA13: U1.26, U8.5
/LCD_DATA14: U1.31, U8.4
/LCD_DATA15: U1.32, U8.3
/LCD_DATA16: U1.33, U8.48
/LCD_DATA17: U1.38, U8.47
/LCD_DATA18: U1.40, U8.46
/LCD_DATA19: U1.41, U8.45
/LCD_DATA20: U1.43, U8.44
/LCD_DATA21: U1.46, U8.43
/LCD_DATA22: U1.48, U8.42
/LCD_DATA23: U1.49, U8.41
/LCD_HSYNC: J1.13, U1.29
/LCD_PCLK: U1.55, U8.24
/LCD_VSYNC: J1.14, U1.30
/LED0: R45.1, U1.35
/LED1: R46.1, U1.37
/LED2: R47.1, U1.50
/LED3: R48.1, U1.51
/LED4: R27.1, U1.52
/MD_BOOT0: R12.2, U1.79
/MD_BOOT1: R11.2, U1.80
/MD_CLKS: R9.2, U1.82
/NMI: R42.1, SW2.1, U1.90
/P1_0: J2.13, U1.149
/P1_1: J2.12, U1.150
/P1_2: J2.11, U1.151
/P1_3: J2.10, U1.152
/P1_4: J2.9, U1.153
/P1_5: J2.8, U1.154
/P1_6: J2.7, U1.155
/P1_7: J2.6, U1.156
/P1_8: J2.21, U1.94
/P1_9: J2.20, U1.95
/P1_10: J2.19, U1.96
/P1_11: J2.18, U1.97
/P1_12: J2.17, U1.98
/P1_13: J2.16, U1.99
/P1_14: J2.15, U1.100
/P1_15: J2.14, U1.101
/P2_7: J2.4, U1.159
/P2_8: J2.3, U1.160
/P2_9: J2.2, U1.161
/P3_15: J2.5, U1.157
/P7_3: J2.31, U1.53
/P7_5: J2.30, U1.56
/P7_6: J2.29, U1.57
/P7_7: J2.28, U1.59
/P7_8: J2.27, U1.60
/P7_9: J2.26, U1.61
/P7_10: J2.25, U1.62
/P7_11: J2.24, U1.63
/P8_12(RXD): J2.23, K1.1, U1.64
/P8_13(TXD): J2.22, K1.3, U1.66
/PLLVCC: C28.1, C76.1, L6.1, U1.85
/PVCC: C1.1, C5.1, C6.1, C7.1, C8.1, C11.1, C11_2.1, C11_3.1, C13.1, C14.1, C15.1, C16.1, C18.1, C19.1, C21_3.1, C21_4.1, C21_5.1, C69.1, C71_2.1, C71_3.1, C73.1, C74.1, L1.2, P7.1, U1.11, U1.25, U1.36, U1.47, U1.58, U1.67, U1.78, U1.93, U1.106, U1.125, U1.130, U1.136, U1.147, U1.195, U1.206
/RAM_A1: U1.119, U5.23
/RAM_A2: U1.120, U5.24
/RAM_A3: U1.122, U5.25
/RAM_A4: U1.124, U5.26
/RAM_A5: U1.126, U5.29
/RAM_A6: U1.131, U5.30
/RAM_A7: U1.132, U5.31
/RAM_A8: U1.133, U5.32
/RAM_A9: U1.138, U5.33
/RAM_A10: U1.139, U5.34
/RAM_A11: U1.141, U5.22
/RAM_A12: U1.142, U5.35
/RAM_A13: U1.144, U5.36
/RAM_A14: U1.146, U5.20
/RAM_A15: U1.148, U5.21
/RAM_CAS: U1.75, U5.17
/RAM_CKE: U1.76, U5.37
/RAM_CLK: P5.1, U1.45, U5.38
/RAM_CS: U1.68, U5.19
/RAM_D0: U1.205, U5.2
/RAM_D1: U1.207, U5.4
/RAM_D2: U1.208, U5.5
/RAM_D3: U1.1, U5.7
/RAM_D4: U1.2, U5.8
/RAM_D5: U1.3, U5.10
/RAM_D6: U1.4, U5.11
/RAM_D7: U1.5, U5.13
/RAM_D8: U1.6, U5.42
/RAM_D9: U1.8, U5.44
/RAM_D10: U1.10, U5.45
/RAM_D11: U1.12, U5.47
/RAM_D12: U1.13, U5.48
/RAM_D13: U1.14, U5.50
/RAM_D14: U1.15, U5.51
/RAM_D15: U1.16, U5.53
/RAM_DQMH: U1.112, U5.39
/RAM_DQML: U1.110, U5.15
/RAM_RAS: U1.69, U5.18
/RAM_RDnWR: U1.158, U5.16
/RESET: C53.2, R20.1, SW1.1, U1.92, U7.1
/SD_CD_1: CON3.G5, R19.2, U1.70
/SD_CLK_1: CON3.5, U1.127
/SD_CMD_1: CON3.3, U1.129
/SD_D0_1: CON3.7, U1.73
/SD_D1_1: CON3.8, U1.72
/SD_D2_1: CON3.1, U1.137
/SD_D3_1: CON3.2, U1.135
/SPBCLK_0: U1.196, U4.6
/SPBIO_00_0: U1.202, U4.5
/SPBIO_10_0: U1.204, U4.2
/SPBIO_20_0: U1.190, U4.3
/SPBIO_30_0: U1.191, U4.7
/SPBSSL_0: U1.197, U4.1
/SW0: R43.1, SW3.1, U1.188
/SW1: R44.1, SW4.1, U1.189
/SYS_CLK: P4.1, R2.1, U1.86
/USBAPVCC: C2.1, C67.1, L4.2, U1.181
/USBAVCC: C29.1, L7.1, U1.182
/USBDPVCC: C1_2.1, C4.1, C68.1, L3.2, U1.165, U1.172
/USBDVCC: C31.1, C32.1, L9.1, U1.170, U1.177
/USBUVCC: C30.1, L8.1, U1.184
/USB_CLK: P3.1, R3.1, U1.163
/VBUS: CON1.1, D6.1, U1.176
/VCC: C17.1, C21.1, C21_2.1, C23.1, C24.1, C25.1, C26.1, C70.1, C71.1, C75.1, L5.1, P8.1, U1.7, U1.21, U1.42, U1.74, U1.111, U1.121, U1.143
/VGAB: J1.1, R26.1, U8.28
/VGAG: J1.2, R25.1, U8.32
/VGAR: J1.3, R24.1, U8.34
unnamed: C36.2, U1.84, X1.1
unnamed: C37.2, U1.83, X1.2
unnamed: C52.1, U7.5
unnamed: C57.1, U8.35
unnamed: C58.1, U8.36
unnamed: D1.1, R45.2
unnamed: D2.1, R46.2
unnamed: D3.1, R47.2
unnamed: D4.1, R48.2
unnamed: D7.1, R51.2
unnamed: D8.1, R27.2
unnamed: R1.2, U1.179
unnamed: R2.2, U2.3
unnamed: R3.2, U3.3
unnamed: R21.1, U8.37
unnamed: R22.2, R23.2, U1.105
VSS: C1.2, C1_2.2, C2.2, C3.2, C4.2, C5.2, C6.2, C7.2, C8.2, C11.2, C11_2.2, C11_3.2, C13.2, C14.2, C15.2, C16.2, C17.2, C18.2, C19.2, C21.2, C21_2.2, C21_3.2, C21_4.2, C21_5.2, C23.2, C24.2, C25.2, C26.2, C28.2, C29.2, C30.2, C31.2, C32.2, C33.1, C34.2, C35.2, C36.1, C37.1, C38.2, C39.2, C40.2, C41.2, C42.2, C43.2, C44.2, C45.2, C46.2, C48.2, C50.2, C51.2, C52.2, C53.1, C54.1, C55.1, C56.1, C57.2, C58.2, C67.2, C68.2, C69.2, C70.2, C71.2, C71_2.2, C71_3.2, C72.2, C73.2, C74.2, C75.2, C76.2, CON1.5, CON1.6, CON1.7, CON1.8, CON1.9, CON2.4, CON3.6, CON3.G1, CON3.G2, CON3.G3, CON3.G4, CON4.2, CON4.3, J1.5, J1.6, J1.7, J1.8, J1.9, J1.10, J2.32, K1.2, P1.3, P1.5, P1.9, P10.1, P11.1, P12.1, P13.1, P14.1, P15.1, P16.1, P17.1, R1.1, R9.1, R10.1, R12.1, R21.2, R23.1, R24.2, R25.2, R26.2, R50.1, R51.1, SW1.2, SW2.2, SW3.2, SW4.2, U1.9, U1.18, U1.23, U1.34, U1.39, U1.44, U1.54, U1.65, U1.77, U1.88, U1.89, U1.91, U1.103, U1.109, U1.118, U1.123, U1.128, U1.134, U1.140, U1.145, U1.162, U1.166, U1.171, U1.173, U1.178, U1.180, U1.183, U1.185, U1.186, U1.187, U1.193, U1.203, U2.2, U3.2, U4.4, U5.6, U5.12, U5.28, U5.41, U5.46, U5.52, U5.54, U6.1, U7.3, U8.1, U8.2, U8.12, U8.14, U8.15, U8.25, U8.26, U8.27, U8.31, U8.33, U8.39, U8.40, U9.1
